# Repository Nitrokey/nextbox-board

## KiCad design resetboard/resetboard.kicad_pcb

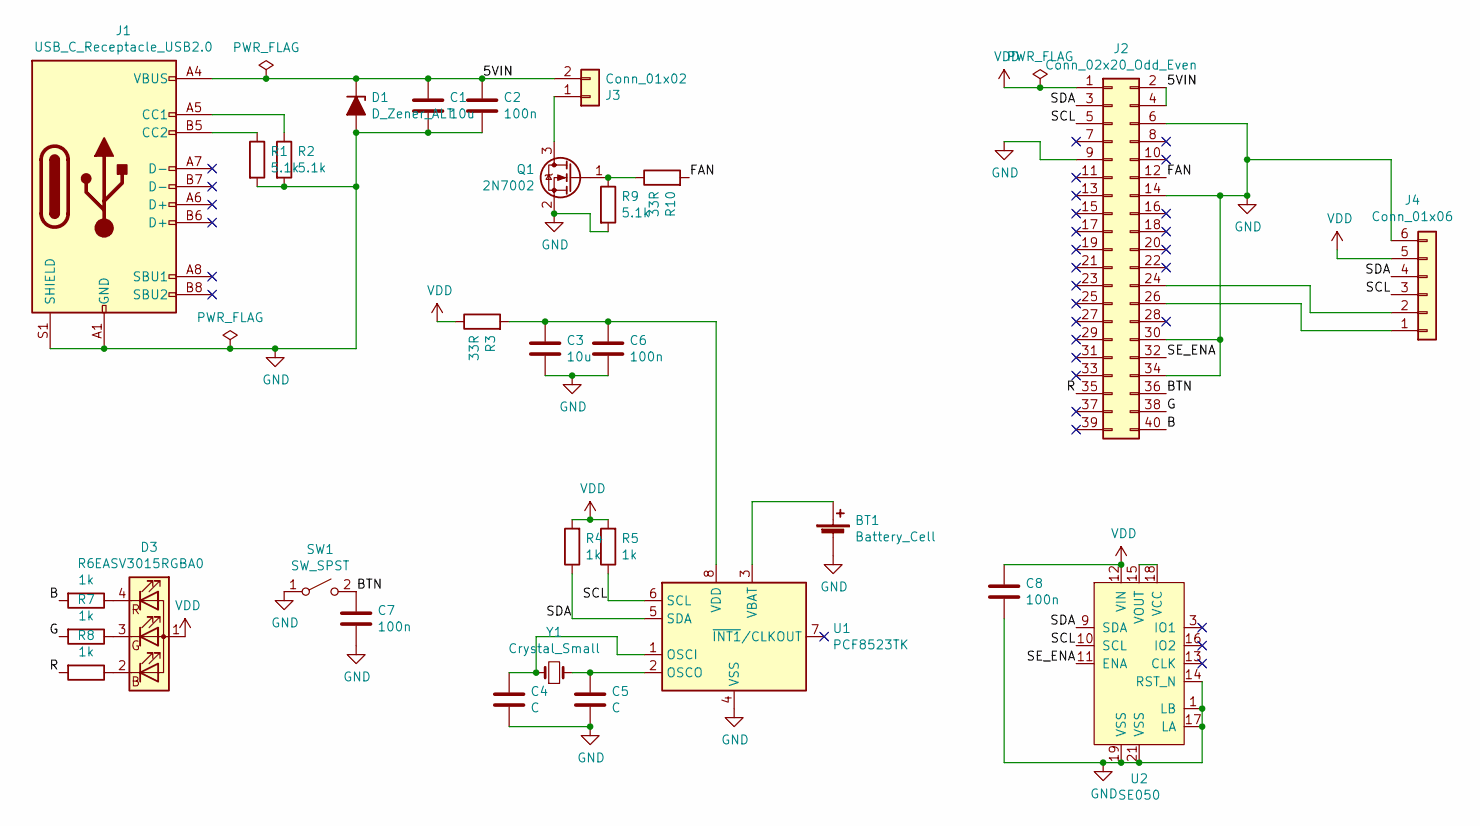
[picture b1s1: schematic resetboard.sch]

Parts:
BT1: Battery_Cell; BatteryHolder_Keystone_3000_1x12mm
C1, C3: 10u; C_0805_2012Metric
C2, C6, C7, C8: 100n; C_0603_1608Metric
C4, C5: C; C_0402_1005Metric
D1: D_Zener_ALT; D_SOD-123
D3: EASV3015RGBA0; HQ12-2353RBGC
J1: USB_C_Receptacle_USB2.0; USB_C_Receptacle_XKB_U262-16XN-4BVC11
J2: Conn_02x20_Odd_Even; PinHeader_2x20_P2.54mm_Vertical
J3: Conn_01x02; JST_GH_SM02B-GHS-TB_1x02-1MP_P1.25mm_Horizontal
J4: Conn_01x06; JST_GH_BM06B-GHS-TBT_1x06-1MP_P1.25mm_Vertical
Q1: 2N7002; SOT-23
R1, R2, R9: 5.1k; R_0603_1608Metric
R3, R10: 33R; R_0603_1608Metric
R4, R5, R6, R7, R8: 1k; R_0603_1608Metric
SW1: SW_SPST; SW_SPST_EVQP7C
U1: PCF8523TK; HVSON-8-1EP_4x4mm_P0.8mm_EP2.2x3.1mm
U2: SE050; UQFN-20-1EP_3x3mm_P0.4mm_EP1.85x1.85mm
Y1: Crystal_Small; Crystal_SMD_2012-2Pin_2.0x1.2mm

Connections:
/5VIN: C1.1, C2.1, D1.1 (K), J1.A4 (VBUS), J1.A9 (VBUS), J1.B4 (VBUS), J1.B9 (VBUS), J2.2, J2.4, J3.2
/B: J2.40, R6.2
/BTN: C7.1, J2.36, SW1.2 (B)
/FAN: J2.12, R10.2
/G: J2.38, R7.2
/R: J2.35, R8.2
/SCL: J2.5, J4.3, R5.1, U1.6 (SCL), U2.10 (SCL)
/SDA: J2.3, J4.4, R4.1, U1.5 (SDA), U2.9 (SDA)
/SE_ENA: J2.32, U2.11 (ENA)
GND: BT1.2 (-), C1.2, C2.2, C3.2, C4.2, C5.2, C6.2, C7.2, C8.2, D1.2 (A), J1.A1 (GND), J1.A12 (GND), J1.B1 (GND), J1.B12 (GND), J1.S1 (SHIELD), J2.6, J2.9, J2.14, J2.30, J2.34, J4.6, Q1.2 (S), R1.2, R2.2, R9.2, SW1.1 (A), U1.4 (VSS), U1.9 (VSS), U2.1 (LB), U2.14 (RST_N), U2.17 (LA), U2.19 (VSS), U2.21 (VSS)
unnamed: BT1.1 (+), U1.3 (VBAT)
unnamed: C3.1, C6.1, R3.2, U1.8 (VDD)
unnamed: C4.1, U1.1 (OSCI), Y1.1
unnamed: C5.1, U1.2 (OSCO), Y1.2
unnamed: D3.2 (BK), R8.1
unnamed: D3.3 (GK), R7.1
unnamed: D3.4 (RK), R6.1
unnamed: J1.A5 (CC1), R2.1
unnamed: J1.B5 (CC2), R1.1
unnamed: J2.24, J4.2
unnamed: J2.26, J4.1
unnamed: J3.1, Q1.3 (D)
unnamed: Q1.1 (G), R9.1, R10.1
unnamed: U2.15 (VOUT), U2.18 (VCC)
VDD: C8.1, D3.1 (A), J2.1, J4.5, R3.1, R4.2, R5.2, U2.12 (VIN)

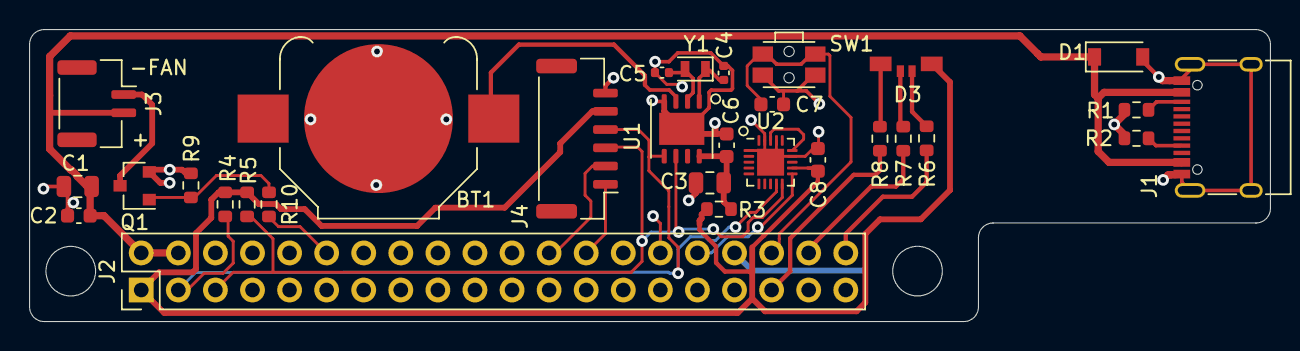
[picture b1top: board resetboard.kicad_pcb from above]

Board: 2 copper layers, 85.0 x 20.0 mm, 30 parts (0 on the bottom side), 25 nets.

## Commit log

2021-02-01 initial proto version
2021-02-22 Remove ziptie holes Add filtering to RTC supply Add NFET-controlled fan on GPIO18 Switch fan connector to horizontal Rearrange parts to move fan connector to left edge of board Rotate LED towards edg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
